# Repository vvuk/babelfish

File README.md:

Babelfish
=========

_This is a work in progress._

Babelfish is a hardware device and associated software to allow using a USB keyboard and mouse on a variety of retro computers.

Planned or in progress emulations include:

* Apollo
  * DN[3-5]XXX, DN10000, HP9000 series 400 with Domain/OS.
  * DN300
* SGI (pre-PS2)
* Sun (pre-PS2)
* Mac ADB
* PS/2 ?

The Sun code is based on the (USB2Sun)[] project.

## Hardware

TBD.

## Building

TBD.

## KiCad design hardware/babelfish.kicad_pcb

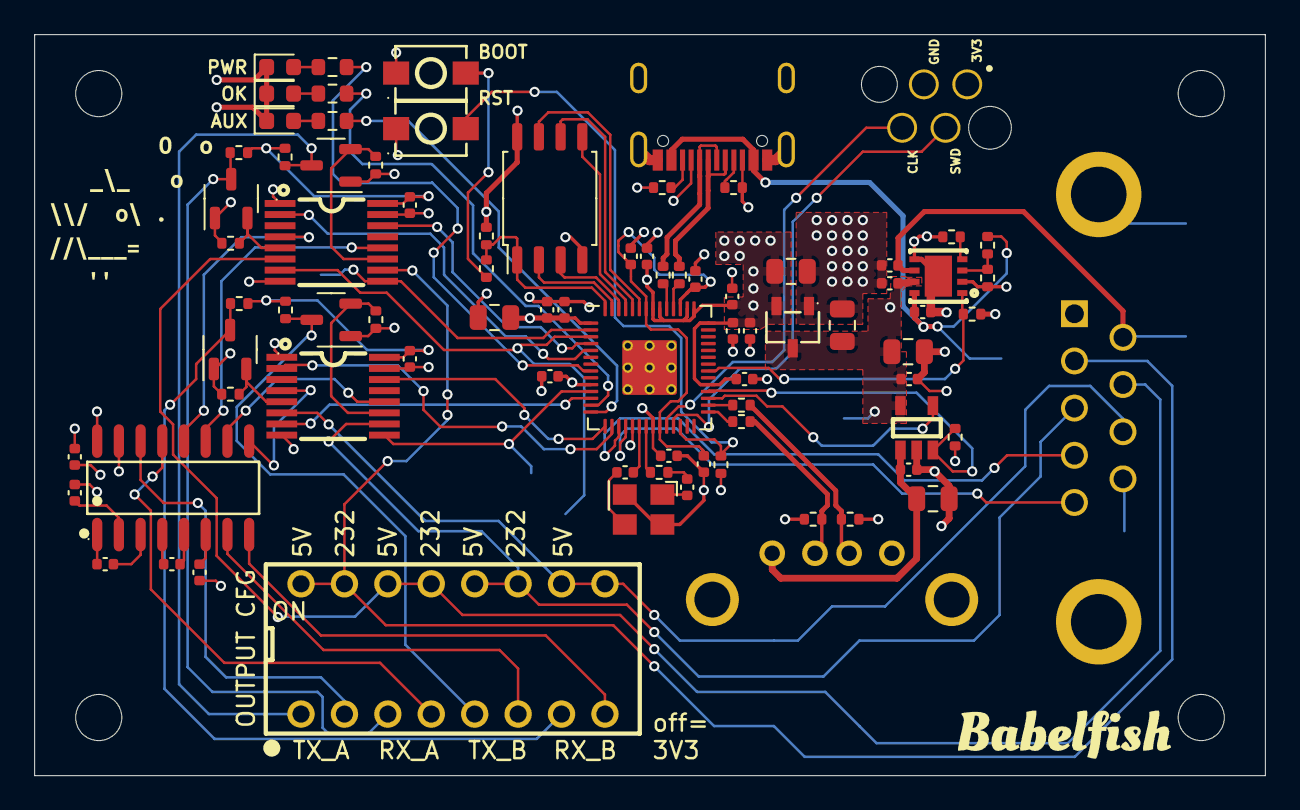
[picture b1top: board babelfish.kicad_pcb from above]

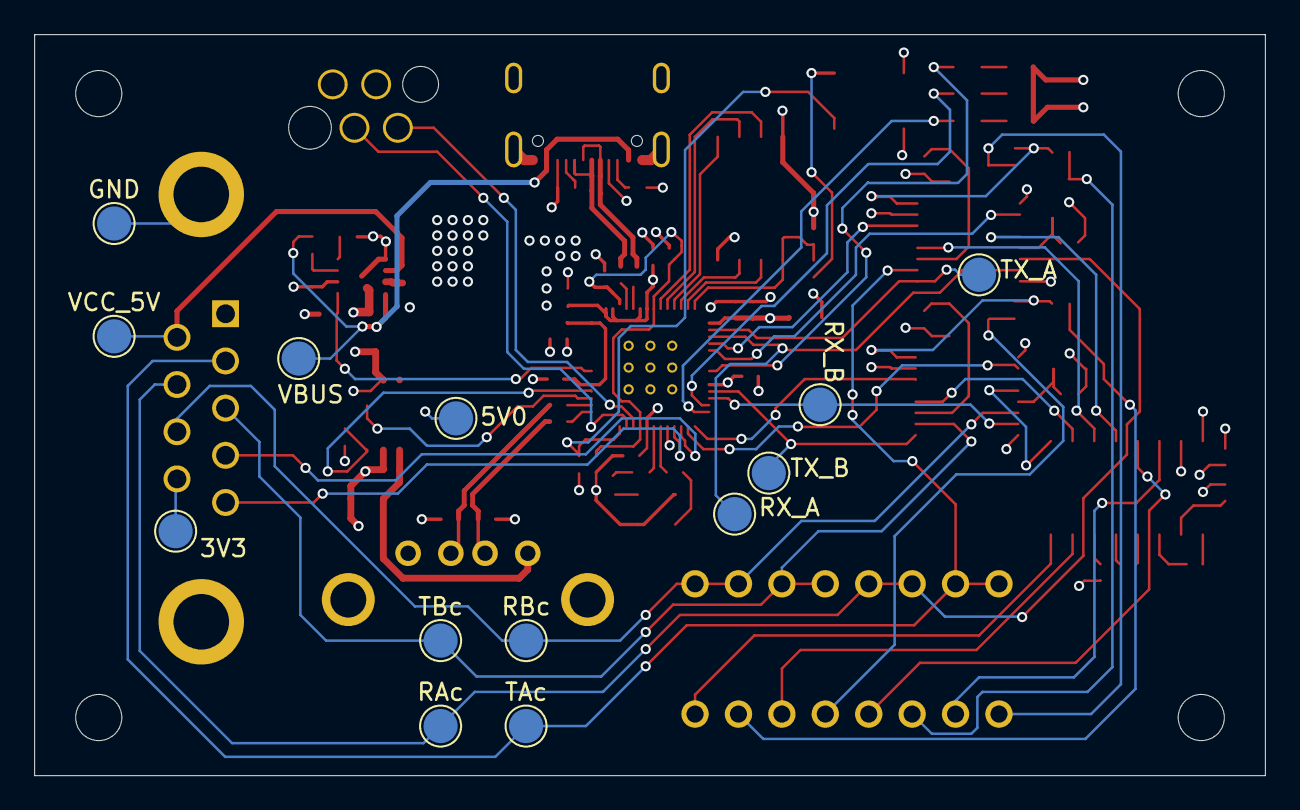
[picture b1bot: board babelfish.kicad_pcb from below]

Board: 4 copper layers, 72.0 x 43.4 mm, 101 parts (13 on the bottom side), 79 nets.

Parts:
3V3, 5V0: TestPoint; TestPoint_Pad_D2.0mm
C1, C2, C4, C5, C6, C7, C8, C9, C10, C15, C16, C18, C23, C24, C25, C26, C27, C28, C30, C36, C37: 100n; C_0402_1005Metric
C3, C21, C22, C29, C31: 10u; C_0805_2012Metric
C11, C12: 30p; C_0402_1005Metric
C13, C14, C17: 1u; C_0402_1005Metric
D1, D2, D3: Red; LED_0603_1608Metric
DIP1: KF1001-08P-R0-GL-DFT-01B; SW-TH_16P-L21.9-W9.9-P2.54-LS7.6
GND: TestPoint; TestPoint_Pad_D2.0mm
H1, H2, H3, H4: MountingHole; MountingHole_2.7mm_M2.5
J2: SWD; 490107670412
J3: DE9 Female; DSUB-TH_DMR-9S
J4: USB_A; USB-A-TH__USB-AF-90
Q1: BSS138; SOT-23-3
Q2, Q3, Q4: SOT-23-3
R1, R11: 1k; R_0402_1005Metric
R2, R14, R18, R19, R20, R21, R22, R23, R24, R25, R28: 10k; R_0402_1005Metric
R3, R4: 27; R_0402_1005Metric
R5, R10: 5.1K; R_0402_1005Metric
R6: 10k2; R_0402_1005Metric
R7: DNF; R_0402_1005Metric
R8: 2k05; R_0402_1005Metric
R9: 1k4; R_0402_1005Metric
R12, R13: 22; R_0402_1005Metric
R15, R16, R17: 1k; R_0603_1608Metric
R26, R27: 15k; R_0402_1005Metric
RAc: TestPoint; TestPoint_Pad_D2.0mm
RBc: TestPoint; TestPoint_Pad_D2.0mm
RX_A: TestPoint; TestPoint_Pad_D2.0mm
RX_B: TestPoint; TestPoint_Pad_D2.0mm
SW1, SW2: TS342A2P-WZ; SW-SMD_L4.0-W2.9-LS5.0
TAc: TestPoint; TestPoint_Pad_D2.0mm
TBc: TestPoint; TestPoint_Pad_D2.0mm
TX_A: TestPoint; TestPoint_Pad_D2.0mm
TX_B: TestPoint; TestPoint_Pad_D2.0mm
U1: RP2040; RP2040-QFN-56
U2: TPS2113ADRBR; SON-8_L3.0-W3.0-P0.65-LS3.0-BL-EP
U3: GT-USB-7010ASV; USB-C-SMD_G-SWITCH_GT-USB-7010ASV
U4: W25Q128JVS; SOIC-8_5.23x5.23mm_P1.27mm
U6: TPMCP1703T-3302E_CB; SOT-23-3_L2.9-W1.6-P1.90-LS2.8-BR
U7, U8: SN74CBT3253CPWR; TSSOP-16_L5.0-W4.4-P0.65-LS6.4-TL
U11: MAX3232IDR; SOIC-16_L9.9-W3.9-P1.27-LS6.0-BL
U12: AP2191WG-7; SOT-25-5_L2.9-W1.6-P0.95-LS2.8-BL
VBUS: TestPoint; TestPoint_Pad_D2.0mm
VCC_5V: TestPoint; TestPoint_Pad_D2.0mm
X1: X322512MSB4SI; OSC-SMD_4P-L3.2-W2.5-BL
kibuzzard-644F39EB: G***; kibuzzard-644F39EB
kibuzzard-644F3679: G***; kibuzzard-644F3679

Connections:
+1V1: C1.1, C2.1, C13.1, U1.23 (DVDD), U1.45 (VREG_VOUT), U1.50 (DVDD)
+3V3: 3V3.1, C3.1, C4.1, C5.1, C6.1, C7.1, C8.1, C9.1, C10.1, C14.1, C16.1, C22.1, C25.1, J2.1, J3.9, Q1.1 (G), Q2.1 (G), Q3.1 (G), Q4.1 (G), R2.2, R7.1, R14.2, R18.1, R20.1, R22.1, R24.1, R28.2, U1.1 (IOVDD), U1.10 (IOVDD), U1.22 (IOVDD), U1.33 (IOVDD), U1.42 (IOVDD), U1.43 (ADC_AVDD), U1.44 (VREG_IN), U1.48 (USB_VDD), U1.49 (IOVDD), U4.8 (VCC), U6.2 (VOUT), U11.16 (VCC)
/5V0: 5V0.1, C17.1, C21.1, C30.1, C31.1, C36.2, C37.2, R19.1, R21.1, R23.1, R25.1, U2.7 (OUT), U6.3 (VIN), U7.16 (VCC), U8.16 (VCC), U12.5 (IN)
/CH_A_S0: U1.4 (GPIO2), U7.14 (S0)
/CH_A_S1: U1.5 (GPIO3), U7.2 (S1)
/CH_B_S0: U1.15 (GPIO12), U8.14 (S0)
/CH_B_S1: U1.16 (GPIO13), U8.2 (S1)
/GPIO14: J3.4, U1.17 (GPIO14)
/GPIO15: J3.5, U1.18 (GPIO15)
/GPIO18: R12.2, U1.29 (GPIO18)
/GPIO19: R13.2, U1.30 (GPIO19)
/LED_AUX: R17.1, U1.14 (GPIO11)
/LED_PWR: R15.1, U1.8 (GPIO6)
/LED_P_OK: R16.1, U1.13 (GPIO10)
/OSC1: C11.1, X1.1 (OSC1)
/OSC1R: C11.2, R1.1
/OSC2: C12.1, X1.3 (OSC2)
/PWR_VSNS: R6.2, R8.1, U2.3 (VSNS)
/QSPI_SCLK: U1.52 (QSPI_SCLK), U4.6 (CLK)
/QSPI_SD0: U1.53 (QSPI_SD0), U4.5 (DI(IO0))
/QSPI_SD1: U1.55 (QSPI_SD1), U4.2 (DO(IO1))
/QSPI_SD2: U1.54 (QSPI_SD2), U4.3 (IO2)
/QSPI_SD3: U1.51 (QSPI_SD3), U4.7 (IO3)
/QSPI_SS: R7.2, R11.1, U1.56 (QSPI_SS), U4.1 (~CS)
/RUN: R14.1, SW2.2, U1.26 (RUN)
/RX_A: RX_A.1, U1.3 (GPIO1), U7.7 (1A)
/RX_A_CONN: DIP1.13 (PIN13), DIP1.14 (PIN14), J3.7, RAc.1, U7.6 (1B1)
/RX_A_MAX: U7.4 (1B3), U11.12 (ROUT1)
/RX_A_MAX_OUT: DIP1.4 (PIN4), U11.13 (RIN1)
/RX_A_SHIFTER: Q1.2 (S), R18.2, U7.5 (1B2)
/RX_A_SHIFTER_OUT: DIP1.3 (PIN3), Q1.3 (D), R19.2
/RX_B: RX_B.1, U1.12 (GPIO9), U8.7 (1A)
/RX_B_CONN: DIP1.9 (PIN9), DIP1.10 (PIN10), J3.8, RBc.1, U8.6 (1B1)
/RX_B_MAX: U8.4 (1B3), U11.9 (ROUT2)
/RX_B_MAX_OUT: DIP1.8 (PIN8), U11.8 (RIN2)
/RX_B_SHIFTER: Q4.2 (S), R24.2, U8.5 (1B2)
/RX_B_SHIFTER_OUT: DIP1.7 (PIN7), Q4.3 (D), R25.2
/STAT_5V0: R2.1, U1.35 (GPIO23), U2.1 (STAT)
/SWCLK: J2.4, U1.24 (SWCLK)
/SWD: J2.2, U1.25 (SWD)
/TX_A: TX_A.1, U1.2 (GPIO0), U7.9 (2A)
/TX_A_CONN: DIP1.15 (PIN15), DIP1.16 (PIN16), J3.2, TAc.1, U7.10 (2B1)
/TX_A_MAX: U7.12 (2B3), U11.11 (DIN1)
/TX_A_MAX_OUT: DIP1.2 (PIN2), U11.14 (DOUT1)
/TX_A_SHIFTER: Q2.2 (S), R20.2, U7.11 (2B2)
/TX_A_SHIFTER_OUT: DIP1.1 (PIN1), Q2.3 (D), R21.2
/TX_B: TX_B.1, U1.11 (GPIO8), U8.9 (2A)
/TX_B_CONN: DIP1.11 (PIN11), DIP1.12 (PIN12), J3.3, TBc.1, U8.10 (2B1)
/TX_B_MAX: U8.12 (2B3), U11.10 (DIN2)
/TX_B_MAX_OUT: DIP1.6 (PIN6), U11.7 (DOUT2)
/TX_B_SHIFTER: Q3.2 (S), R22.2, U8.11 (2B2)
/TX_B_SHIFTER_OUT: DIP1.5 (PIN5), Q3.3 (D), R23.2
/USB2_D+: J4.3 (D+), R13.1, R27.1
/USB2_D-: J4.2 (D-), R12.1, R26.1
/USB2_EN: U1.31 (GPIO20), U12.4 (EN)
/USB2_FLG: R28.1, U1.32 (GPIO21), U12.3 (FLG)
/USB_D+: R3.1, U3.A6 (DP1), U3.B6 (DP2)
/USB_D-: R4.1, U3.A7 (DN1), U3.B7 (DN2)
/USB_DN: R4.2, U1.46 (USB_DM)
/USB_DP: R3.2, U1.47 (USB_DP)
/VBUS_OUT: C28.1, C29.1, J4.1 (VBUS), U12.1 (OUT)
/VCC_5V: C18.1, J3.6, U2.6 (IN2), VCC_5V.1
/XIN: C12.2, U1.20 (XIN)
/XOUT: R1.2, U1.21 (XOUT)
/~USB_BOOT: R11.2, SW1.2
GND: C1.2, C2.2, C3.2, C4.2, C5.2, C6.2, C7.2, C8.2, C9.2, C10.2, C13.2, C14.2, C15.2, C16.2, C17.2, C18.2, C21.2, C22.2, C23.1, C25.2, C27.2, C28.2, C29.2, C30.2, C31.2, C36.1, C37.1, D1.1 (K), D2.1 (K), D3.1 (K), GND.1, J2.3, J3.1, J3.10 (PAD), J3.11 (PAD), J4.4 (GND), J4.5 (Shield), R5.2, R8.2, R9.2, R10.2, R26.2, R27.2, SW1.1, SW2.1, U1.19 (TESTEN), U1.57 (GND), U2.2 (EN#), U2.5 (GND), U2.9 (EP), U3.1 (SHELL), U3.2 (SHELL), U3.3 (SHELL), U3.4 (SHELL), U3.A1B12 (GND), U3.A8 (SBU1), U3.B1A12 (GND), U3.B8 (SBU2), U4.4 (GND), U6.1 (GND), U7.1 (1OE#), U7.8 (GND), U7.15 (2OE#), U8.1 (1OE#), U8.8 (GND), U8.15 (2OE#), U11.15 (GND), U12.2 (GND), X1.2 (GND), X1.4 (GND)
unnamed: D1.2 (A), R15.2
unnamed: D2.2 (A), R16.2
unnamed: D3.2 (A), R17.2
unnamed: R9.1, U2.4 (ILIM)
unnamed: R10.1, U3.A5 (CC1)
unnamed: R5.1, U3.B5 (CC2)
unnamed: C24.1, U11.1 (C1+)
unnamed: C24.2, U11.3 (C1-)
unnamed: C26.1, U11.4 (C2+)
unnamed: C26.2, U11.5 (C2-)
unnamed: C23.2, U11.2 (V+)
unnamed: C27.1, U11.6 (V-)
VBUS: C15.1, R6.1, U2.8 (IN1), U3.A4B9 (VBUS), U3.B4A9 (VBUS), VBUS.1

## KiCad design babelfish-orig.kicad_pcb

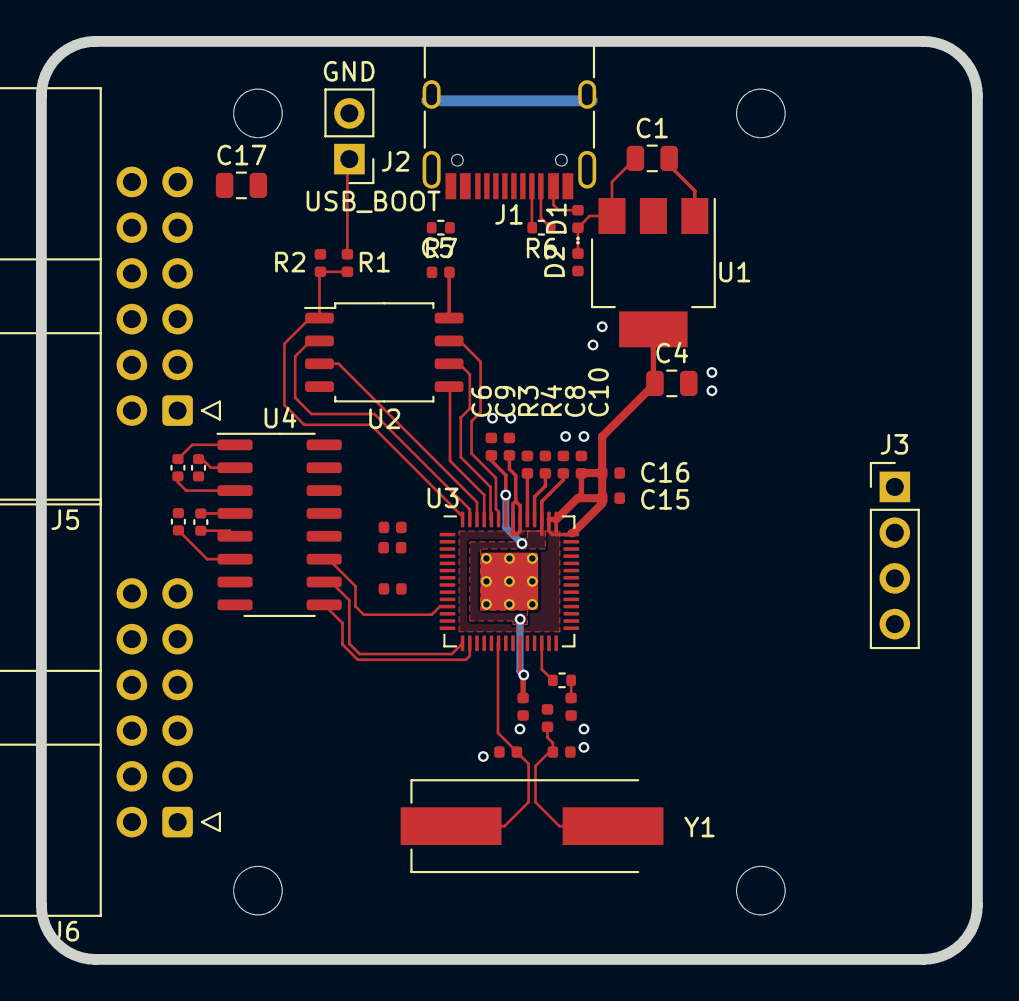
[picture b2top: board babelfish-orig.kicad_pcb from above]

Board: 4 copper layers, 52.0 x 51.0 mm, 45 parts (0 on the bottom side), 51 nets.

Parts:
C1, C4, C17: 10u; C_0805_2012Metric
C2, C3: 27p; C_0402_1005Metric
C5, C6, C7, C9, C11, C12, C13, C14, C15, C16: 100n; C_0402_1005Metric
C8, C10: 1u; C_0402_1005Metric
C18, C19, C20, C21: 0.1uf; C_0402_1005Metric
D1, D2: 1N4001; D_0402_1005Metric
H1, H2, H3, H4: MountingHole; MountingHole_2.7mm_M2.5
J1: USB_C_Receptacle_USB2.0; USB_C_Receptacle_HRO_TYPE-C-31-M-12
J2: Conn_01x02; PinHeader_1x02_P2.54mm_Vertical
J3: SWD; PinHeader_1x04_P2.54mm_Vertical
J5: IO_A; IDC-Header_2x06_P2.54mm_Horizontal
J6: IO_B; IDC-Header_2x06_P2.54mm_Horizontal
R1, R5: 1k; C_0402_1005Metric
R2: DNF; C_0402_1005Metric
R3, R4: 27; C_0402_1005Metric
R6, R7: 5.1K; R_0402_1005Metric
R8: 10k; R_0402_1005Metric
U1: NCP1117-3.3_SOT223; SOT-223-3_TabPin2
U2: W25Q128JVS; SOIC-8_5.23x5.23mm_P1.27mm
U3: RP2040; RP2040-QFN-56
U4: SP3232CPE; SOIC-16_3.9x9.9mm_P1.27mm
Y1: ABLS-12.000MHZ-B4-T; Crystal_SMD_HC49-US

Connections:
+1V1: C6.1, C7.1, C8.1, U3.23 (DVDD), U3.45 (VREG_VOUT), U3.50 (DVDD)
+3V3: C4.1, C5.1, C9.1, C10.1, C11.1, C12.1, C13.1, C14.1, C15.1, C16.1, C17.1, C20.2, J3.1, R2.1, R8.1, U1.2 (VO), U2.8 (VCC), U3.1 (IOVDD), U3.10 (IOVDD), U3.22 (IOVDD), U3.33 (IOVDD), U3.42 (IOVDD), U3.43 (ADC_AVDD), U3.44 (VREG_IN), U3.48 (USB_VDD), U3.49 (IOVDD), U4.16 (VCC)
+5V: D1.2 (A), J1.A4 (VBUS), J1.A9 (VBUS), J1.B4 (VBUS), J1.B9 (VBUS)
/GPIO6: J5.2, U3.8 (GPIO6)
/GPIO7: J5.4, U3.9 (GPIO7)
/GPIO20: J5.8, U3.31 (GPIO20)
/GPIO21: J5.6, U3.32 (GPIO21)
/GPIO26: J6.2, U3.38 (GPIO26_ADC0)
/GPIO27: J6.4, U3.39 (GPIO27_ADC1)
/GPIO28: J6.6, U3.40 (GPIO28_ADC2)
/GPIO29: J6.8, U3.41 (GPIO29_ADC3)
/QSPI_SCLK: U2.6 (CLK), U3.52 (QSPI_SCLK)
/QSPI_SD0: U2.5 (DI(IO0)), U3.53 (QSPI_SD0)
/QSPI_SD1: U2.2 (DO(IO1)), U3.55 (QSPI_SD1)
/QSPI_SD2: U2.3 (IO2), U3.54 (QSPI_SD2)
/QSPI_SD3: U2.7 (IO3), U3.51 (QSPI_SD3)
/QSPI_SS: R1.1, R2.2, U2.1 (~CS), U3.56 (QSPI_SS)
/RUN: R8.2, U3.26 (RUN)
/SWCLK: J3.3, U3.24 (SWCLK)
/SWD: J3.2, U3.25 (SWD)
/U0_232_RX: J6.3, U4.8 (R1IN)
/U0_232_TX: J6.1, U4.7 (T1OUT)
/U0_RX_A: J5.3, U3.3 (GPIO1)
/U0_RX_B: U3.16 (GPIO13), U4.9 (R1OUT)
/U0_TX_A: J5.1, U3.2 (GPIO0)
/U0_TX_B: U3.15 (GPIO12), U4.10 (T1IN)
/U1_232_RX: J6.7, U4.13 (R2IN)
/U1_232_TX: J6.5, U4.14 (T2OUT)
/U1_RX_A: J5.7, U3.7 (GPIO5)
/U1_RX_B: U3.12 (GPIO9), U4.12 (R2OUT)
/U1_TX_A: J5.5, U3.6 (GPIO4)
/U1_TX_B: U3.11 (GPIO8), U4.11 (T2IN)
/USB_D+: J1.A6 (D+), J1.B6 (D+), R3.1
/USB_D-: J1.A7 (D-), J1.B7 (D-), R4.1
/XIN: C2.1, U3.20 (XIN), Y1.1
/XOUT: R5.1, U3.21 (XOUT)
/~USB_BOOT: J2.1, R1.2
GND: C1.2, C2.2, C3.2, C4.2, C5.2, C6.2, C7.2, C8.2, C9.2, C10.2, C11.2, C12.2, C13.2, C14.2, C15.2, C16.2, C17.2, C21.1, J1.A1 (GND), J1.A8 (SBU1), J1.A12 (GND), J1.B1 (GND), J1.B8 (SBU2), J1.B12 (GND), J1.S1 (SHIELD), J2.2, J3.4, J5.10, J6.10, R6.1, R7.1, U1.1 (GND), U2.4 (GND), U3.19 (TESTEN), U3.57 (GND), U4.15 (GND)
unnamed: C1.1, D1.1 (K), D2.1 (K), U1.3 (VI)
unnamed: C3.1, R5.2, Y1.2
unnamed: C19.1, U4.4 (C2+)
unnamed: C19.2, U4.5 (C2-)
unnamed: C20.1, U4.2 (V+)
unnamed: C21.2, U4.6 (V-)
unnamed: J1.A5 (CC1), R6.2
unnamed: J1.B5 (CC2), R7.2
unnamed: R3.2, U3.47 (USB_DP)
unnamed: R4.2, U3.46 (USB_DM)
unnamed: C18.1, U4.1 (C1+)
unnamed: C18.2, U4.3 (C1-)
VBUS: D2.2 (A), J5.9, J6.9

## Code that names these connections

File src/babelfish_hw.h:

#ifndef BABLEFISH_H_
#define BABELFISH_H_

#define HW_REV 0x03

#if HW_REV >= 0x02
// Channel A pins
#define TX_A_GPIO 0
#define RX_A_GPIO 1

// Mux selection for channel A.
//
// 0 = direct
// 1 = via level shifter
// 2 = via MAX3232
#define CH_A_S0_GPIO 2
#define CH_A_S1_GPIO 3

// Channel B pins
#define TX_B_GPIO 8
#define RX_B_GPIO 9

// Mux selection for channel B.
// v0.2 these are floating unless they are patched
// v0.3 only -- these were not connected on v0.2, oops.
#define CH_B_S0_GPIO 12
#define CH_B_S1_GPIO 13

// Babelfish v0.2 has LEDs on these three GPIOs,
// typically used for power indications and an aux indicator.
#define LED_PWR_GPIO 6
#define LED_P_OK_GPIO 10
#define LED_AUX_GPIO 11

// The secondary USB port has D- on GPIO 18 and D+ on GPIO 19.
#define USB_AUX_DM_GPIO 18
#define USB_AUX_DP_GPIO 19

// The USB 5V controller breaks out a status signal, connected to GPIO 23.
#define USB_AUX_EN_GPIO 20
#define USB_AUX_FLG_GPIO 21
#define USB_5V_STAT_GPIO 23
#endif

typedef enum {
    ChannelModeDirect = 0,
    ChannelModeLevelShifter = 1,
    ChannelMode232 = 2,
    ChannelModeOutputMask = 0x0f,

    ChannelModeGPIO = 0 << 4, // configure this channel as bare GPIO
    ChannelModeUART = 1 << 4, // configure this channel as a UART
    ChannelModeOutputTypeMask = 0xf0,

    ChannelModeNoInvert = 0 << 8, // don't invert output
    ChannelModeInvert = 1 << 8, // invert output
    ChannelModeInvertMask = 0xf00,

    // Direct GPIO, 3.3v
    ChannelConfigDirect = ChannelModeDirect | ChannelModeGPIO | ChannelModeNoInvert,

    // Direct GPIO, through level shifter (5v or vcc)
    ChannelConfigDirectShifted = ChannelModeLevelShifter | ChannelModeGPIO | ChannelModeNoInvert,

    // UART -- TTL, shifted (5v or vcc)
    ChannelConfigUARTShifted = ChannelModeDirect | ChannelModeGPIO | ChannelModeInvert,

    // UART -- RS232 through MAX3232
    ChannelConfigRS232 = ChannelMode232 | ChannelModeUART | ChannelModeInvert,
} ChannelMode;

typedef struct ChannelConfig {
    uint8_t channel_num;
    uint8_t uart_num;
    uint8_t tx_gpio;
    uint8_t rx_gpio;
    uint8_t mux_s0_gpio;
    uint8_t mux_s1_gpio;

    ChannelMode mode;
} ChannelConfig;

#define NUM_CHANNELS 2

extern ChannelConfig channels[NUM_CHANNELS];

extern void channel_config(int channel_num, ChannelMode mode);

#endif

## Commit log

2023-01-22 Abstract away host
2023-01-22 adb checkpoint
2023-01-22 More adb WIP
2023-01-22 Apollo WIP
2023-01-26 add pio-usb
2023-02-04 initial
2023-02-05 Fix apollo
2023-03-02 Add submodule
2023-03-03 Add debug
2023-03-04 More Apollo & debug work
2023-03-06 tweak debug and apollo output
2023-03-13 Reorganize
2023-05-13 rev 0.1
2023-05-26 rev2, pre review
2023-05-30 notes and pico debugging
2023-08-20 remove pico-pio-usb
2023-08-21 compiling
2023-08-21 Abstract away UART
2023-08-21 rename to babelfish, move output
2023-08-22 don't use tinyusb bsp, fix event processing
2023-08-24 Rework debug
2023-08-26 remove bsp/board.h and fixes
2023-08-26 Add openocd flash
2023-08-26 HID updates
2023-08-27 stdio uart, hid_app, bootmode processing, debugging
2023-09-06 usb serial debug; working-ish apollo
2023-09-12 apollo mouse
2023-09-30 Moved files aroud. WIP new power section
2023-09-30 Power section done
2023-10-01 Added muxes
2023-10-01 Layout v2 done
2023-10-02 V2 export WIP
2023-10-05 Update LICENSE
2023-10-07 Er, forgot to wire CH_B_S0/1
2023-10-12 Move description to HostDevice
2023-10-12 Add equal-command handling
2023-10-13 enable usb aux power
2023-10-14 reindent
2023-10-15 hw: Add back test points to schematic, fix db9 GND
2023-10-15 Remove stdio_usb, drive cdc directly
2023-10-16 Re-enable babelfish-test
2023-11-03 hw v0.3
2023-11-03 misc tweaks
2023-11-05 WIP fixing the mux/demux
2023-11-06 more dip switch replacements
2023-11-07 Move 5V power to TPS62933, from WEBENCH
2023-11-07 WIP new power
2023-11-11 WIP -- pre-shift-up
2023-11-11 WIP dip switches
2023-11-18 Finished complex DC-DC layout, pre-deletion
2023-11-20 add host-test, set it
2024-03-30 hwtest
2024-03-31 v3 rc0
2024-03-31 v3 rc2
2024-03-31 v3 production
2024-04-04 adapters md
2024-04-04 misc
2024-04-11 docs and adb
2024-04-12 fix test
2024-05-12 Fix adb isr type
2024-05-12 Just bring a copy of stdio_usb in for sanity
2024-05-12 Enable aux usb and more nusb tweaks
2024-05-13 Add B reboot, tweak protocol/report mode
2024-05-25 proper invert setup for apollo
2024-05-27 Apollo works, after mouse fix
2024-06-30 add a fallback return false
2024-06-30 mostly c&p the host_apollo stuff over. starting to make dn300 tweaks
2024-08-14 add a rj45 diagram and the babelfish connections
2024-08-14 update the readme
2024-08-14 remove some of the c&p mouse code
2024-08-14 might as well remove this comment - it's not about the dn300 setup
2024-08-14 vscode
2024-08-14 Add mac build workflow
2024-08-15 Fixes for pico-sdk 2.0
2024-08-15 master -> main
2024-08-17 adb docs
2024-08-17 Add NeXT support
2025-09-16 Add v2 schematic pdf
2025-09-16 Add schematic pdf
